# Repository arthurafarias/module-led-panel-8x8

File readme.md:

# LED Panel 8x8

This repository contains the KiCad project and documentation for a stackable 8×8 LED matrix module. The design is intended for creating compact LED display tiles that can be chained together to build larger matrices.

## Overview

The module includes a compact 8×8 LED array laid out for standard matrix control. The board is designed with stacking in mind, so several modules can be tiled together to expand the display area while keeping the wiring and layout manageable.

There is no dedicated connector interface on the module. Boards are linked by aligning and soldering their castellated side pads together.

Key characteristics of this project:

- 64 SMD LEDs arranged in an 8×8 matrix
- Stackable module design for building larger LED displays
- KiCad schematic and PCB layout included
- Front and back visuals are available in `docs/`

## Usage

- Use the module with a matrix driver or microcontroller to control rows and columns.
- Chain multiple modules together to create larger display panels.
- Verify the LED current limiting strategy and wiring for your selected driver or controller.

## Project structure

- `module-led-panel-8x8.kicad_pro` — KiCad project file
- `module-led-panel-8x8.kicad_sch` — schematic source
- `module-led-panel-8x8.kicad_pcb` — PCB layout file
- `docs/index.html` — project showcase and documentation page
- `docs/module-led-panel-8x8-front.png` — front view image
- `docs/module-led-panel-8x8-back.png` — back view image
- `docs/module-led-panel-8x8-perspective.png` — perspective view image

## Notes

This repository is focused on the LED matrix module itself. The board uses castellated side pads so panels can be soldered together for tiling, instead of relying on a separate connector interface.

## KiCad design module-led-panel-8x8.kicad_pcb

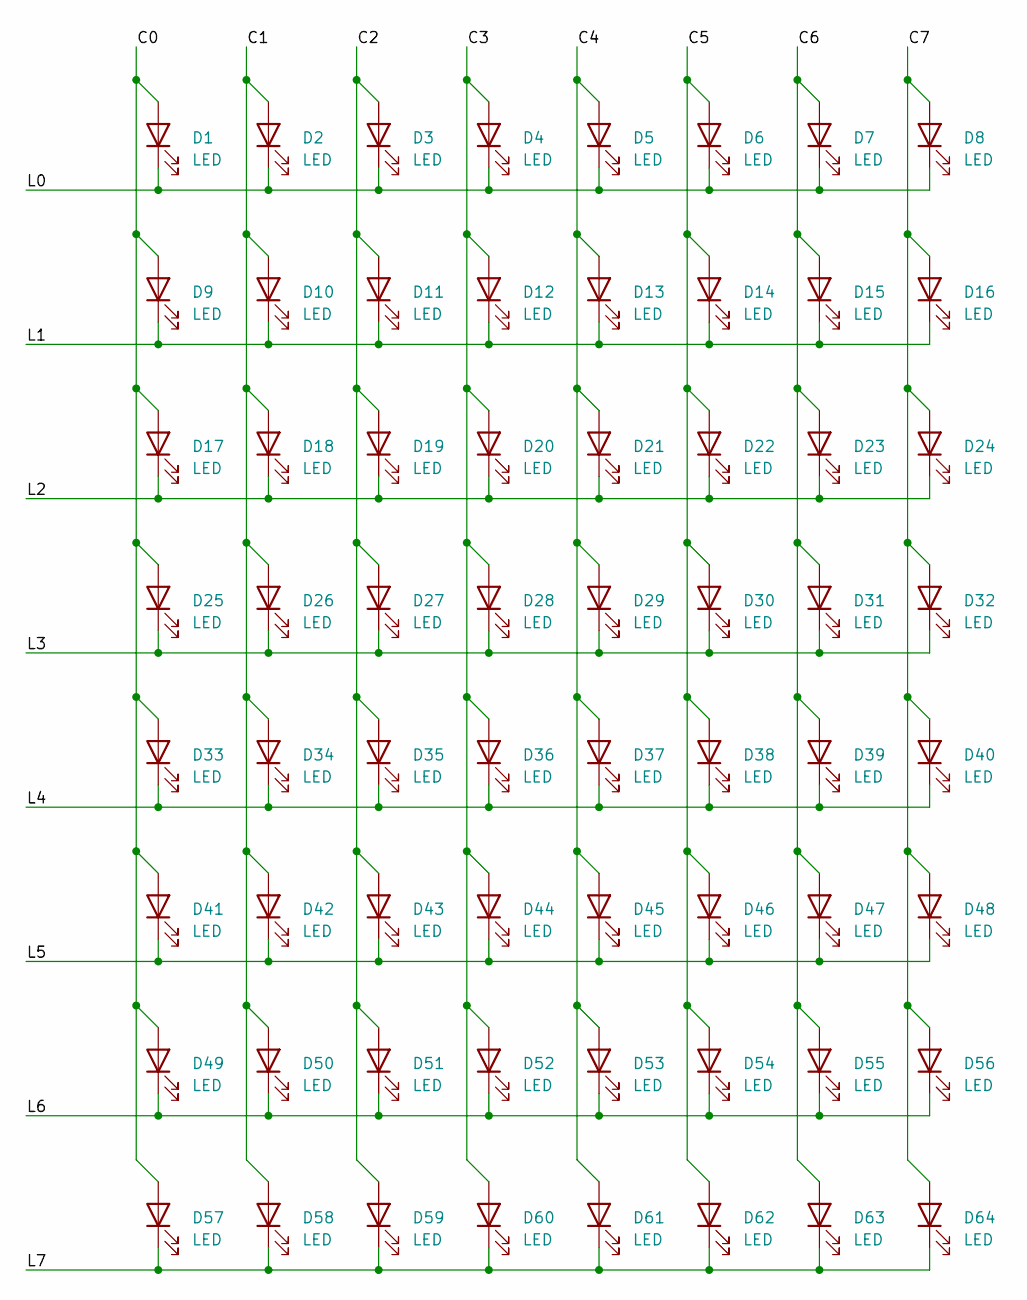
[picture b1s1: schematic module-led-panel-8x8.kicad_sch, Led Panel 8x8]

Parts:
D1, D2, D3, D4, D5, D6, D7, D8, D9, D10, D11, D12, D13, D14, D15, D16, D17, D18, D19, D20, D21, D22, D23, D24, D25, D26, D27, D28, D29, D30, D31, D32, D33, D34, D35, D36, D37, D38, D39, D40, D41, D42, D43, D44, D45, D46, D47, D48, D49, D50, D51, D52, D53, D54, D55, D56, D57, D58, D59, D60, D61, D62, D63, D64: LED; LED_0808_2020Metric

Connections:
/C0: D1.2 (A), D9.2 (A), D17.2 (A), D25.2 (A), D33.2 (A), D41.2 (A), D49.2 (A), D57.2 (A)
/C1: D2.2 (A), D10.2 (A), D18.2 (A), D26.2 (A), D34.2 (A), D42.2 (A), D50.2 (A), D58.2 (A)
/C2: D3.2 (A), D11.2 (A), D19.2 (A), D27.2 (A), D35.2 (A), D43.2 (A), D51.2 (A), D59.2 (A)
/C3: D4.2 (A), D12.2 (A), D20.2 (A), D28.2 (A), D36.2 (A), D44.2 (A), D52.2 (A), D60.2 (A)
/C4: D5.2 (A), D13.2 (A), D21.2 (A), D29.2 (A), D37.2 (A), D45.2 (A), D53.2 (A), D61.2 (A)
/C5: D6.2 (A), D14.2 (A), D22.2 (A), D30.2 (A), D38.2 (A), D46.2 (A), D54.2 (A), D62.2 (A)
/C6: D7.2 (A), D15.2 (A), D23.2 (A), D31.2 (A), D39.2 (A), D47.2 (A), D55.2 (A), D63.2 (A)
/C7: D8.2 (A), D16.2 (A), D24.2 (A), D32.2 (A), D40.2 (A), D48.2 (A), D56.2 (A), D64.2 (A)
/L0: D1.1 (K), D2.1 (K), D3.1 (K), D4.1 (K), D5.1 (K), D6.1 (K), D7.1 (K), D8.1 (K)
/L1: D9.1 (K), D10.1 (K), D11.1 (K), D12.1 (K), D13.1 (K), D14.1 (K), D15.1 (K), D16.1 (K)
/L2: D17.1 (K), D18.1 (K), D19.1 (K), D20.1 (K), D21.1 (K), D22.1 (K), D23.1 (K), D24.1 (K)
/L3: D25.1 (K), D26.1 (K), D27.1 (K), D28.1 (K), D29.1 (K), D30.1 (K), D31.1 (K), D32.1 (K)
/L4: D33.1 (K), D34.1 (K), D35.1 (K), D36.1 (K), D37.1 (K), D38.1 (K), D39.1 (K), D40.1 (K)
/L5: D41.1 (K), D42.1 (K), D43.1 (K), D44.1 (K), D45.1 (K), D46.1 (K), D47.1 (K), D48.1 (K)
/L6: D49.1 (K), D50.1 (K), D51.1 (K), D52.1 (K), D53.1 (K), D54.1 (K), D55.1 (K), D56.1 (K)
/L7: D57.1 (K), D58.1 (K), D59.1 (K), D60.1 (K), D61.1 (K), D62.1 (K), D63.1 (K), D64.1 (K)

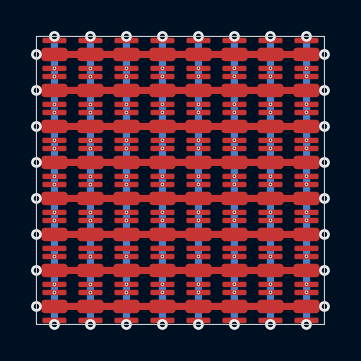
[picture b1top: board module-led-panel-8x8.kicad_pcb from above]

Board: 2 copper layers, 16.0 x 16.0 mm, 64 parts (0 on the bottom side), 16 nets.
